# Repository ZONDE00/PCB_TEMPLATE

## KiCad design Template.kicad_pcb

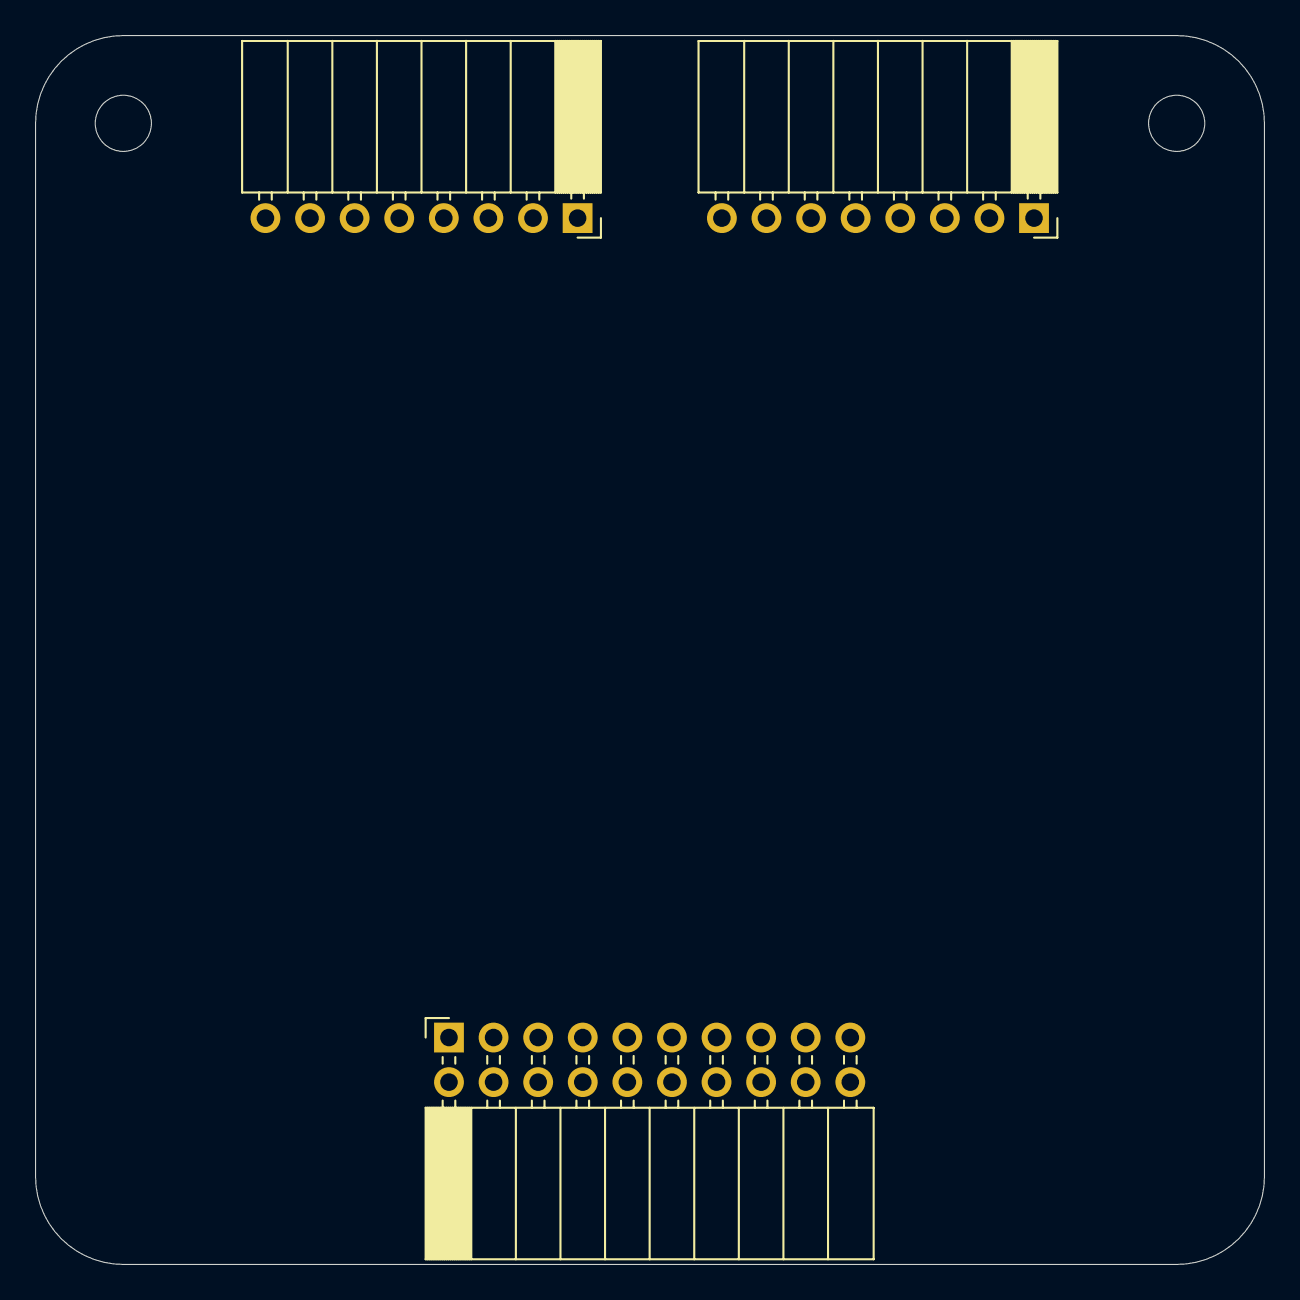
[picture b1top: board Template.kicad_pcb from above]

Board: 2 copper layers, 70.0 x 70.0 mm, 5 parts (0 on the bottom side), 3 nets, no tracks yet.

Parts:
H1, H2: MountingHole; MountingHole_3.2mm_M3
J1: Conn_02x10_Odd_Even; PinSocket_2x10_P2.54mm_Horizontal
J2, J3: Conn_01x08; PinSocket_1x08_P2.54mm_Horizontal

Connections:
+3V3: J1.17, J1.18
+4V: J1.3, J1.4
GND: J1.1, J1.2, J1.19, J1.20, J2.1, J2.2, J3.7, J3.8

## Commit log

2022-08-13 0.1 version
    Template 0.1 V for all subsystems
2022-08-13 Placed things in metrics not with rnd()
2022-08-13 Added gitignore
2022-08-13 Small edit
2022-09-18 CONNECTOR
    Main connector position adjustment.
